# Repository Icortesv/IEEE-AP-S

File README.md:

# TRIPLE-T TEAM

Welcome! Before starting we want to say that there are
still a lot of things to do in this project. The idea is 
to keep improving and learn a lot in the meantime.

## TOPIC

A DOA and RSS-based Localization Radio System with a CPW-Fed Monopole Array Antenna at the ISM 5.8 GHz Band

## Topics included
	- Antenna Theory
	- Analog Design (RF components development)
	- Hardware Design (FPGAs)
	- Algorithm Development (1. MATLAB, 2. Software Application, 
		3. Hardware Design in FPGA, if possible)
	- Software Applications (from device drivers to GUIs)
	- ...

## Project Structure

	Bibliography --> Important background before starting.

	HD --> Hardware Design: Designed boards.

	LHT --> Localization Hardware Toolkit: Designed Hardware designs. 

	LST --> Localization Software Toolkit: Designed User applications. 

	MLT --> MATLAB Localization Toolkit: Designed simulations. 

	Petalinux --> Petalinux environmet: Designed device drivers and useful recommendations. 

## Any questions? Contact us!

* Iñigo Cortés --> icortesv@ieee.org
* Fátima Villa --> a903997@alumni.unav.es
* Álvaro Urain --> a904590@alumni.unav.es

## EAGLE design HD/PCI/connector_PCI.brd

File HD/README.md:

# Hardware Design
## Toolkits 

We have used Eagle because of previous experience in other projects. 

Other recommendations: DesignSpark (easy), KiCad EDA, Allegro (advance). 

## Boards

* PCI: It is a PCI to GPIO Adapter. It connects the output of the ADC to the GPIOs of the Zynqberry.

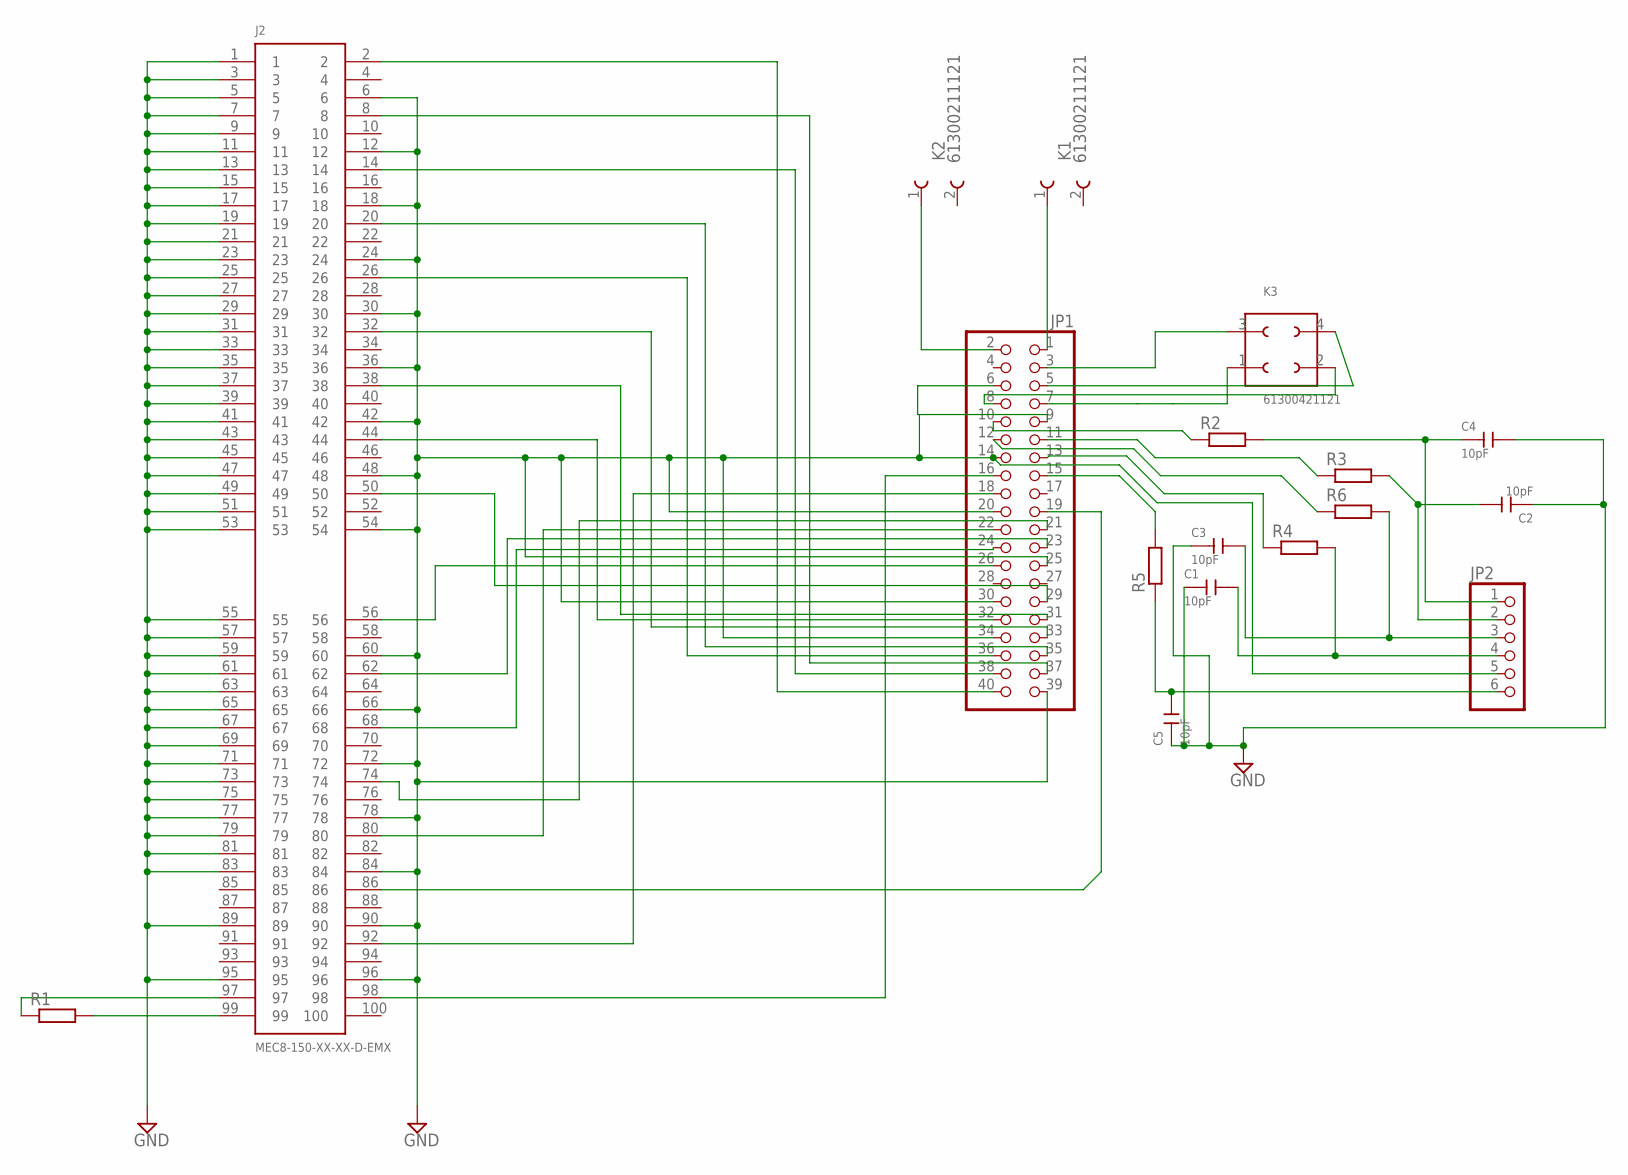
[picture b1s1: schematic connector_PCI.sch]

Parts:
C1, C2, C3, C4, C5: 10pF; C0603
J2: MEC8-150-XX-XX-D-EMX
JP1: PINHD-2X20_2.54; 2X20
JP2: PINHD-1X06_2.54; 1X06
K1, K2: 61300211121
K3: 61300421121
R1, R2, R3, R4, R5, R6: R-EU_R0402; R0402

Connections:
GND: C1.1, C2.1, C3.1, C4.2, C5.1, J2.1, J2.3, J2.5, J2.6, J2.7, J2.9, J2.11, J2.12, J2.13, J2.15, J2.17, J2.18, J2.19, J2.21, J2.23, J2.24, J2.25, J2.27, J2.29, J2.30, J2.31, J2.33, J2.35, J2.36, J2.37, J2.39, J2.41, J2.42, J2.43, J2.45, J2.47, J2.48, J2.49, J2.51, J2.53, J2.54, J2.55, J2.57, J2.59, J2.60, J2.61, J2.63, J2.65, J2.66, J2.67, J2.69, J2.71, J2.72, J2.73, J2.75, J2.77, J2.78, J2.79, J2.81, J2.83, J2.84, J2.89, J2.90, J2.95, J2.96, JP1.6, JP1.9, JP1.14, JP1.20, JP1.25, JP1.30, JP1.34, JP1.39, JP2.5
unnamed: J2.2, JP1.40
unnamed: J2.50, JP1.29
unnamed: J2.8, JP1.37
unnamed: C4.1, JP2.1, R2.2
unnamed: J2.14, JP1.38
unnamed: J2.20, JP1.35
unnamed: J2.26, JP1.36
unnamed: J2.32, JP1.33
unnamed: J2.38, JP1.31
unnamed: JP1.1, K1.1
unnamed: JP1.2, K2.1
unnamed: J2.44, JP1.32
unnamed: J2.62, JP1.23
unnamed: JP1.8, K3.2 (3)
unnamed: JP1.5, K3.4
unnamed: J2.56, JP1.26
unnamed: JP1.7, K3.1 (2)
unnamed: J2.97, R1.1
unnamed: J2.99, R1.2
unnamed: JP1.3, K3.3 (1)
unnamed: JP1.10, R2.1
unnamed: J2.68, JP1.24
unnamed: J2.98, JP1.16
unnamed: C3.2, JP2.3, R6.2
unnamed: C1.2, JP2.4, R4.2
unnamed: J2.74, JP1.21
unnamed: C5.2, JP2.6, R5.1
unnamed: J2.80, JP1.22
unnamed: J2.86, JP1.19
unnamed: J2.92, JP1.18
unnamed: JP1.11, R3.1
unnamed: JP1.13, R4.1
unnamed: JP1.15, R5.2
unnamed: JP1.12, R6.1
unnamed: C2.2, JP2.2, R3.2

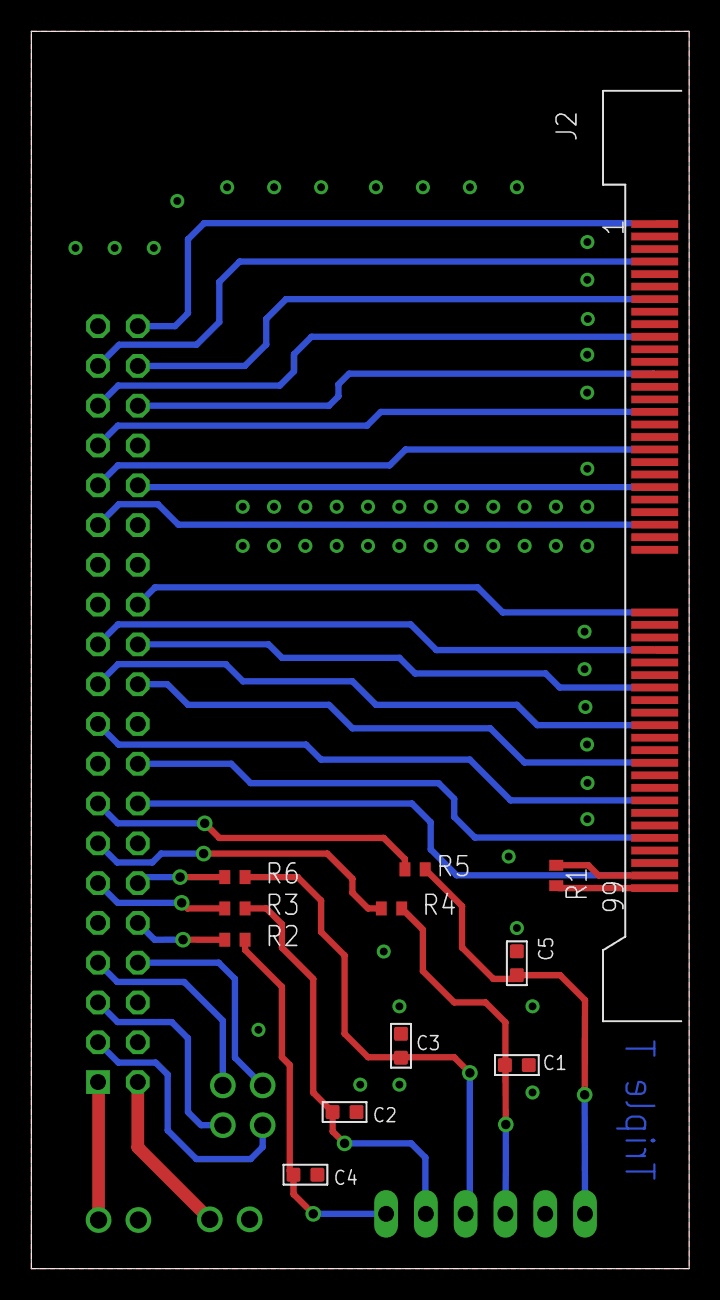
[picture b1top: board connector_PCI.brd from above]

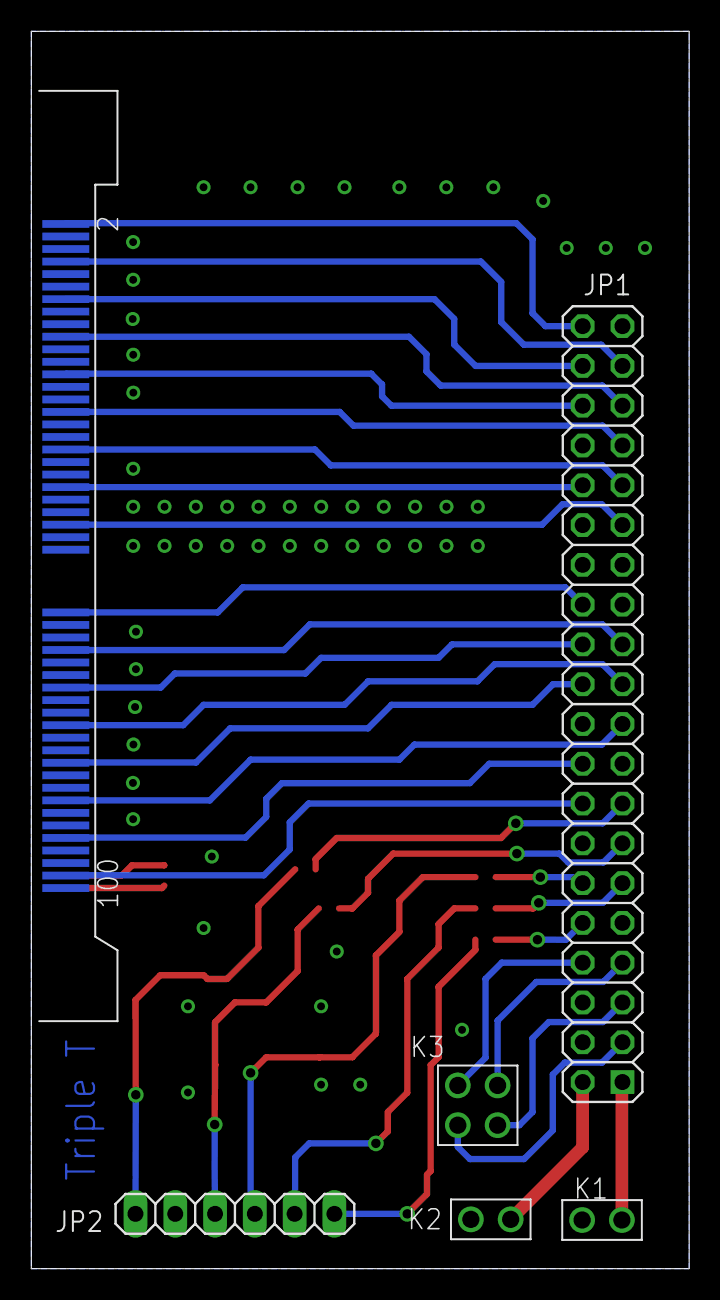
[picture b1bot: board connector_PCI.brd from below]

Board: 2 copper layers, 42.0 x 79.0 mm, 17 parts (5 on the bottom side), 36 nets.

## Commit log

2018-10-20 test_1
2018-11-17 Added first structure.
2018-11-17 Added Petalinux folder.
2018-11-17 readmes update
2019-03-03 LST: systems: dspapp: test space
2019-03-21 LST: systems:dspapp: Update coding style
2019-03-21 LST: systems: dspapp: Update coding style
2019-03-23 LST: systems: dspapp: Update application structure
2019-03-25 LST: systems: dactest: Add 2nd complement to integer application
2019-06-10 LST: systems: antennadir: Refactor antennadir application
2019-06-10 LST: systems: dspapp: Refactor dspapp application
2019-06-10 MLT: Matalb_Plots_Codes: Plot Receiver Measurements: Add code to plot channel sounding
2019-06-10 MLT: Matlab_Plots_Codes: Plot S11: Add code to plot S11
2019-06-10 MLT: Update README
